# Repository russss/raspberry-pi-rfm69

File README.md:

# Raspberry Pi RFM69 Interface

This is a Raspberry Pi interface to the HopeRF RFM69 module, designed
for the [UKHASnet](https://ukhas.net) project.

It supports up to 4 channels with independent RFM69 transceivers, intended
for experimenting with sectored antennas and long-range backhaul links,
but can also be used with just a single RFM69 for more normal applications.

For code which works with this, check out my [rfm69
python library](https://github.com/russss/rfm69-python).

## BOM

To use just a single RFM69 channel, you will need:

* IC1: RFM69[H][W]
* J1: 40-pin socket (e.g. Farnell 7992033)
* P1: Edge-launch SMA socket

To use more than one RFM69, you'll additionally need:

* IC5: 3.3V 800mA regulator in SOT-223 package e.g. NCP1117 (Farnell 1652366)
* C1, C2: 10uF 0805 SMD capacitors
* IC6: 74HC139 Demultiplexer, TSSOP-16 (Farnell 2444981)
* Plus additional RFM69s and SMA sockets

To use one-wire sensors if you require a strong pull-up:

* R1: A 4k7 0805 SMD resistor

## Assembly

If you want to use a single RFM69, you'll need to bridge jumpers J1 and
J2. J1 connects the 3v3 bus to the RPi's (which will *just about* run
one RFM69 from my experience).

J2 bypasses the demultiplexer on the SPI chip select line and
connects it directly to the first RFM69.

## Pin Mappings

|Module | Interrupt (DIO0) | Reset  |
|-------|------------------|--------|
|1      | GPIO20           | GPIO21 |
|2      | GPIO02           | GPIO03 |
|3      | GPIO27           | GPIO22 |
|4      | GPIO19           | GPIO26 |

* 1-wire: GPIO4
* NSS Select: GPIO23 (bit 1), GPIO24 (bit 2)

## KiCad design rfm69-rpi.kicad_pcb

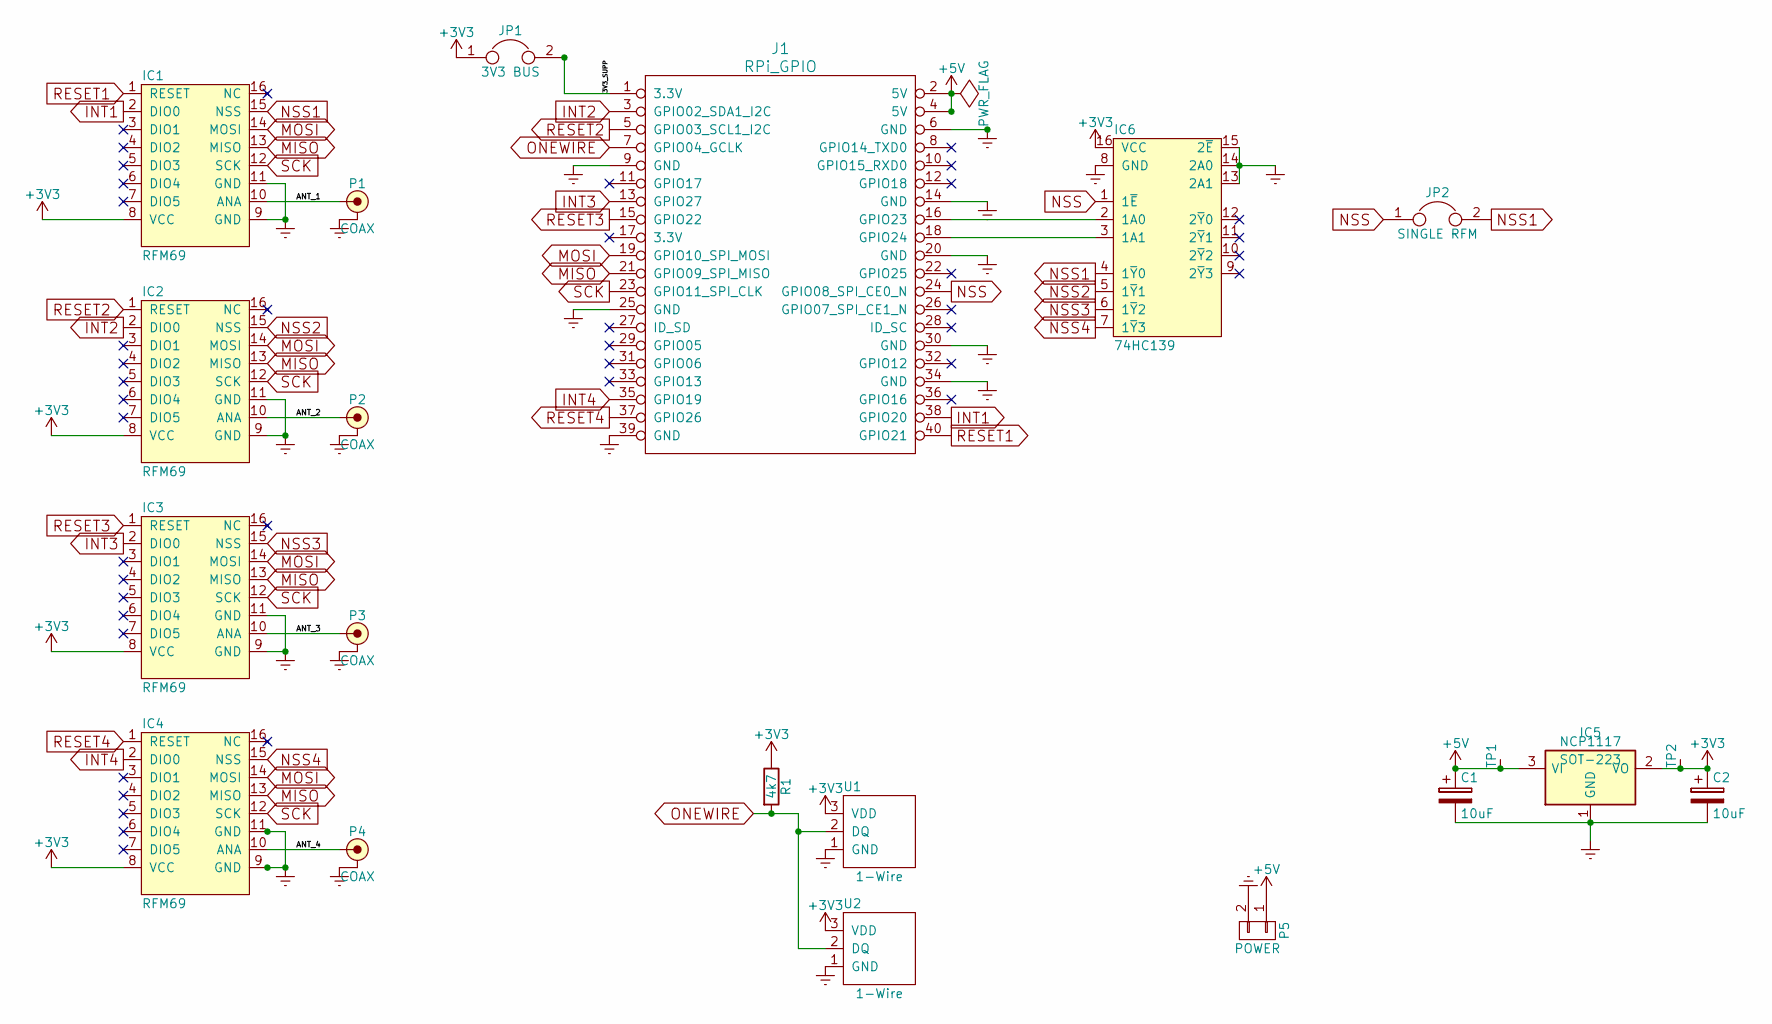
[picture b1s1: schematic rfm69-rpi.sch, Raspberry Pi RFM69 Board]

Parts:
C1, C2: 10uF; C_0805
IC1, IC2, IC3, IC4: RFM69
IC5: NCP1117; SOT-223
IC6: 74HC139; TSSOP-16; Farnell 2444981
J1: RPi_GPIO; raspberrypi2
JP1: 3V3 BUS; TESTPT
JP2: SINGLE RFM; TESTPT
P1, P2, P3, P4: COAX; SMA-EDGE; Farnell 1608592
P5: POWER; JST-PH-SM4-2
R1: 4k7; 0805
TP1, TP2: TESTPAD
U1, U2: 1-Wire; TO-92_Molded_Narrow

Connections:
+3V3: C2.1, IC1.8 (VCC), IC2.8 (VCC), IC3.8 (VCC), IC4.8 (VCC), IC5.2 (VO), IC6.16 (VCC), JP1.1, R1.1, TP2.1, U1.3 (VDD), U2.3 (VDD)
+5V: C1.1, IC5.3 (VI), J1.2 (5V), J1.4 (5V), P5.1, TP1.1
/3V3_SUPP: J1.1 (3.3V), JP1.2
/ANT_1: IC1.10 (ANA), P1.1 (RF)
/ANT_2: IC2.10 (ANA), P2.1 (RF)
/ANT_3: IC3.10 (ANA), P3.1 (RF)
/ANT_4: IC4.10 (ANA), P4.1 (RF)
Earth: C1.2, C2.2, IC1.9 (GND), IC1.11 (GND), IC2.9 (GND), IC2.11 (GND), IC3.9 (GND), IC3.11 (GND), IC4.9 (GND), IC4.11 (GND), IC5.1 (GND), IC5.4, IC6.8 (GND), IC6.13 (2A1), IC6.14 (2A0), IC6.15 (2~E), J1.6 (GND), J1.9 (GND), J1.14 (GND), J1.20 (GND), J1.25 (GND), J1.30 (GND), J1.34 (GND), J1.39 (GND), P1.2 (GND), P2.2 (GND), P3.2 (GND), P4.2 (GND), P5.2, U1.1 (GND), U2.1 (GND)
INT1: IC1.2 (DIO0), J1.38 (GPIO20)
INT2: IC2.2 (DIO0), J1.3 (GPIO02_SDA1_I2C)
INT3: IC3.2 (DIO0), J1.13 (GPIO27)
INT4: IC4.2 (DIO0), J1.35 (GPIO19)
MISO: IC1.13 (MISO), IC2.13 (MISO), IC3.13 (MISO), IC4.13 (MISO), J1.21 (GPIO09_SPI_MISO)
MOSI: IC1.14 (MOSI), IC2.14 (MOSI), IC3.14 (MOSI), IC4.14 (MOSI), J1.19 (GPIO10_SPI_MOSI)
NSS: IC6.1 (1~E), J1.24 (GPIO08_SPI_CE0_N), JP2.1
NSS1: IC1.15 (NSS), IC6.4 (1~Y~0), JP2.2
NSS2: IC2.15 (NSS), IC6.5 (1~Y~1)
NSS3: IC3.15 (NSS), IC6.6 (1~Y~2)
NSS4: IC4.15 (NSS), IC6.7 (1~Y~3)
unnamed: IC6.2 (1A0), J1.16 (GPIO23)
unnamed: IC6.3 (1A1), J1.18 (GPIO24)
ONEWIRE: J1.7 (GPIO04_GCLK), R1.2, U1.2 (DQ), U2.2 (DQ)
RESET1: IC1.1 (RESET), J1.40 (GPIO21)
RESET2: IC2.1 (RESET), J1.5 (GPIO03_SCL1_I2C)
RESET3: IC3.1 (RESET), J1.15 (GPIO22)
RESET4: IC4.1 (RESET), J1.37 (GPIO26)
SCK: IC1.12 (SCK), IC2.12 (SCK), IC3.12 (SCK), IC4.12 (SCK), J1.23 (GPIO11_SPI_CLK)

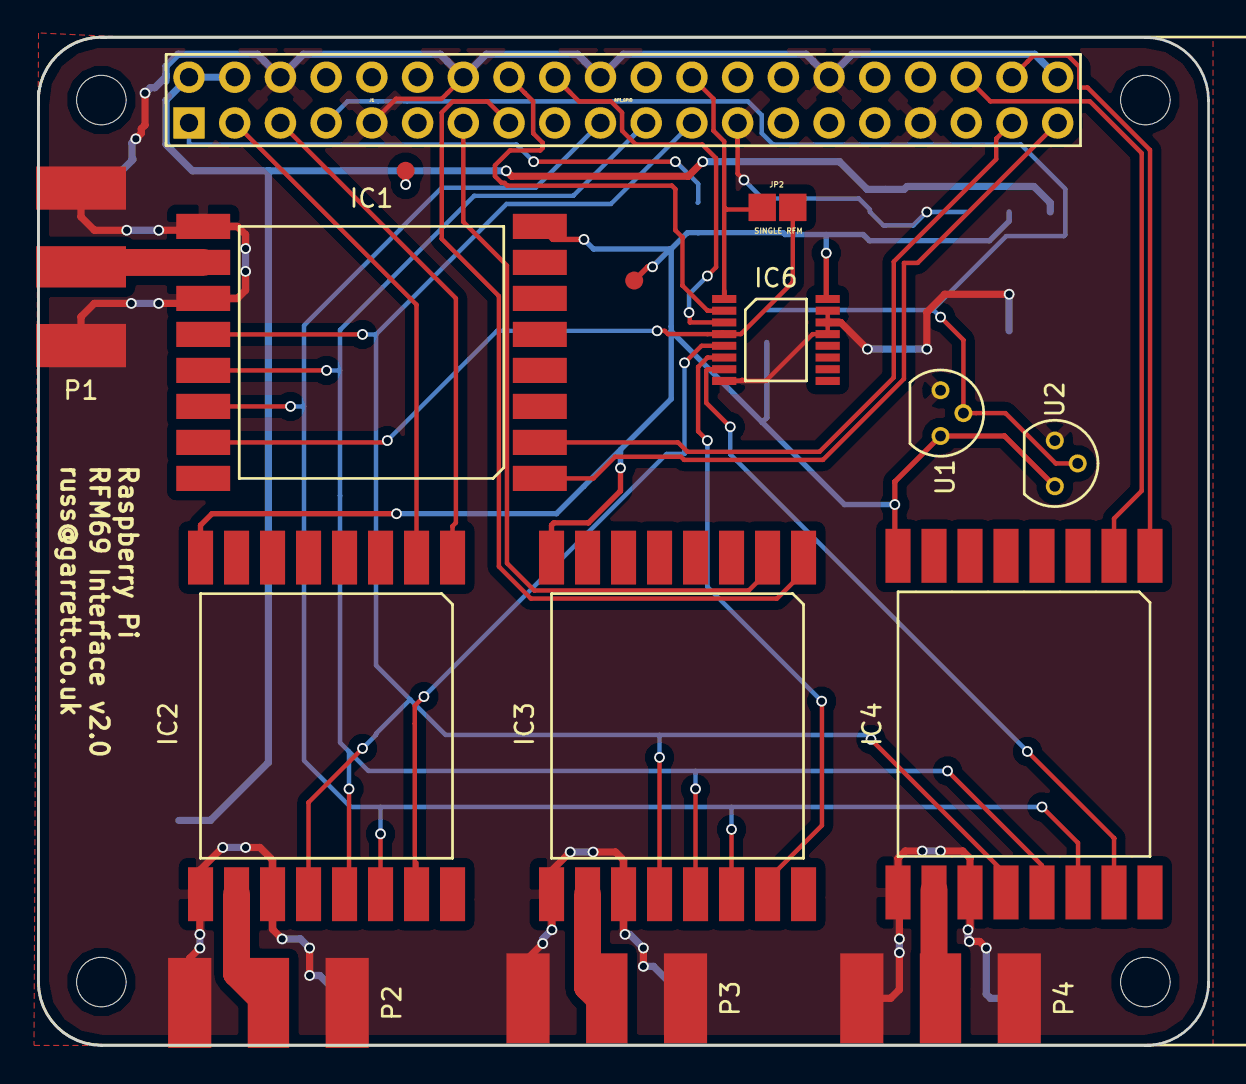
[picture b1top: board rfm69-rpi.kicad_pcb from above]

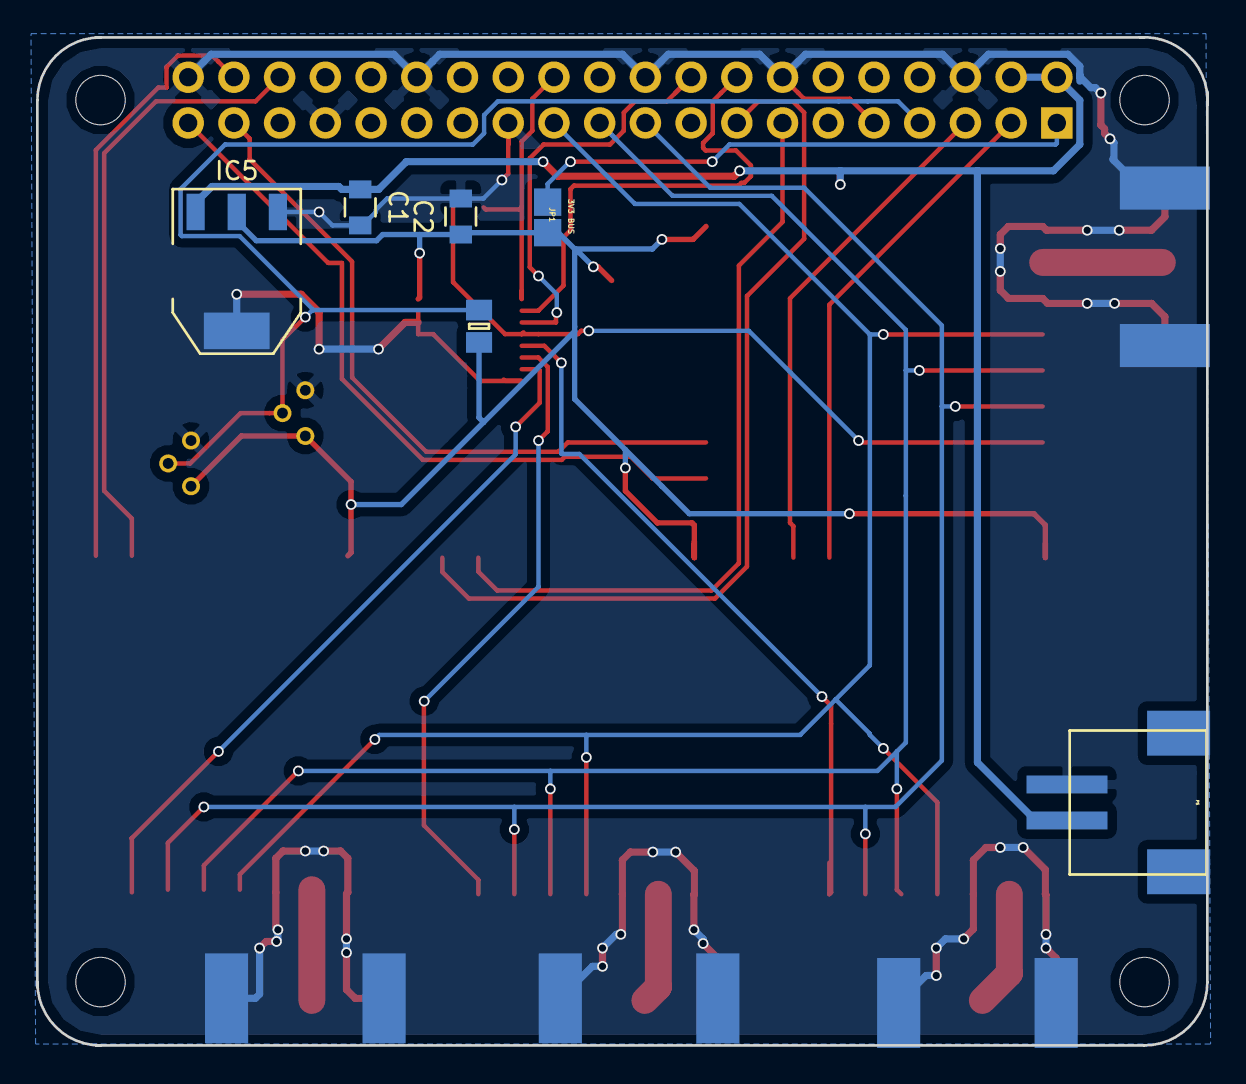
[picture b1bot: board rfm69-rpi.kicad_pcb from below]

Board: 2 copper layers, 65.0 x 56.0 mm, 21 parts (6 on the bottom side), 27 nets.

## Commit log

2016-09-12 Version 2
2016-09-12 Readme update
2016-09-12 Add CERN OHL
2016-09-12 Readme tweak
2016-09-13 Version 2.0
